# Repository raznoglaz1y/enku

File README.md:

<h1 align="center">ENKU</h1>

<p align="center">
  <strong>A pocketable e-reader you can actually own — repairable, local-first, distraction-free.</strong>
</p>

<p align="center">
  A focused, low-power 3.97″ reader with physical controls, local file management, no account or cloud requirement, and a documented, extensible hardware/software stack.
</p>

<p align="center">
  <strong>Project website:</strong> <a href="https://enkureader.com">enkureader.com</a>
</p>

<p align="center">
  <strong>UI languages:</strong> EN · PL · DE · FR · ES · IT · RU
</p>

---

## What is ENKU?

ENKU is a compact e-reader project currently validated around the **Waveshare ESP32-S3-ePaper-3.97** platform with an **800 × 480** e-paper display, while a dedicated portrait-first ENKU mainboard is being developed in parallel. The 3.97″ target is intentional: R0.1 remains a genuinely pocketable reader rather than growing into a small conventional e-reader.

The goal is not to reproduce a full tablet or build a feature-heavy general-purpose device. ENKU is intended to be a **small, calm and purpose-built reader**: fast enough for books, simple to operate, comfortable to use offline, and understandable from both the software and hardware side.

The project is being developed as a complete product system rather than only a firmware demo. It includes:

- firmware and device architecture;
- a complete non-touch UI for physical controls;
- library and reading workflows;
- typography and per-book settings;
- Wi-Fi and local browser-based file management;
- storage and import flows;
- sleep and power-management behavior;
- enclosure development and mechanical iterations;
- reproducible documentation for the hardware, firmware and enclosure;
- a custom ENKU mainboard and costed path toward small-batch community / kit builds.

> **Current status:** firmware architecture and reader runtime are actively implemented, while the custom ENKU R0.1 mainboard is in late routing / pre-production verification. Power routing and the USB-C connector/ESD/CC area have clean native KiCad checkpoints; USB data completion, dock/unrouted closure, final mechanical/electrical audit and the manufacturing package remain before fabrication. Features are only treated as complete when their repository checks or physical validation support that claim.

### Looking for hardware partners and component suppliers

ENKU is currently looking for **hardware partners, distributors and component suppliers** interested in supporting the development of the project.

The most useful forms of support at this stage are:

- Waveshare ESP32-S3-ePaper-3.97 development units;
- Li-Po batteries suitable for a compact e-reader enclosure;
- buttons, switches, fasteners and other enclosure hardware;
- prototype and replacement components for hardware testing;
- project discounts or sample units;
- technical information about supplied components;
- support for future hardware revisions and enclosure prototypes.

Partners can be credited in the project documentation and repository as hardware partners or component suppliers where appropriate.

The goal is to build ENKU around readily available, reproducible parts rather than one-off or inaccessible hardware.

For partnership or supply discussions, please open an issue or contact the project owner through GitHub.

## Custom mainboard and future kits

The reference Waveshare platform is useful for firmware bring-up, but ENKU is also being engineered as its own compact hardware platform.

The custom mainboard roadmap targets:
- ESP32-S3 + 3.97″ e-paper in a portrait-first PCB;
- physical page controls, hard power-off, BMI270 motion/orientation sensing and magnetic-cover support;
- USB-C as the primary charge/data connector;
- optional magnetic pogo/dock charging;
- a warm adjustable frontlight path promoted to production-candidate research after repeated community feedback;
- Pro-ready frontlight and wireless-charging population options;
- one core PCB that can support Base / Cover / Pro variants through DNP/population choices.

After validation, the project may offer small-batch **electronics kits, Base kits, magnetic-cover kits and Pro/frontlight kits**. These are planned possibilities rather than products currently for sale; final contents and pricing depend on tested hardware, sourcing, compliance and fulfillment.

The intent is to keep DIY builds fully documented even if assembled kits become available.

### Product decisions after the first community review

The first broad r/ereader review sharpened the product direction rather than changing the Pocket target. ENKU R0.1 stays at **3.97″**. The strongest recurring feedback was that open source alone is not enough differentiation, so the project is prioritizing the parts that must be better at the hardware/product level: **repairability, physical controls, battery life, screen-to-body ratio, direct USB storage access and a credible warm-frontlight path**.

The firmware roadmap now includes **USB Mass Storage / direct microSD access**, **Markdown reading**, and logical control remapping for left/right-handed use in portrait and landscape. CrossPoint compatibility will be investigated rather than treating community firmware as something ENKU should exclude.

A separate **compact 4.7–5.2″, preferably 4:3** hardware direction is being researched for later; it is not a replacement for the pocket 3.97″ device.

### R0.1 engineering checkpoint — October 2026

The dedicated ENKU mainboard has progressed beyond placement into detailed routing and verification. The current working baseline is intentionally kept **green in native KiCad CI** while remaining USB and dock routing is iterated.

Fabrication is gated on:

- complete USB D+/D− routing through connector-side ESD and series tuning resistors to ESP32-S3;
- dock detect/power closure and an explicit **zero-unrouted-connections** check;
- final power, EPD high-voltage, return-path, antenna keepout, connector-edge and repairability review;
- final footprint/orientation and mechanical-access audit;
- reproducible Gerber, NC drill, BOM and pick-and-place outputs plus a final PCBWay viewer review.

A green DRC alone is not considered a fabrication release: R0.1 must also pass the explicit connectivity and manufacturing gates above.

## Support ENKU

ENKU is developed publicly, while production-sensitive engineering may remain private until it is mature enough to release. You can help the project without spending money:

- **Star the repository** to make the project easier to discover.
- **Test and report issues** when firmware and hardware builds are available.
- **Contribute** code, documentation, translations, UI feedback, hardware notes or enclosure work — see [CONTRIBUTING.md](CONTRIBUTING.md).
- **Share ENKU** with people interested in open hardware, e-paper and compact readers.

GitHub Sponsors is the project's primary funding channel. Sponsorships help cover development hardware, prototype boards, batteries, enclosure iterations and other direct project costs.

**Sponsor ENKU:** https://github.com/sponsors/raznoglaz1y

Project contact and support page: **https://enkureader.com/contact**

## Follow the project

ENKU is entering its first public community-feedback stage. The immediate goal is to validate the reader, the custom R0.1 hardware and the mechanical design with e-reader, maker and repairability communities before any manufacturing commitment is made.

A **small production run / crowdfunding campaign is being considered after hardware validation**, but no campaign, launch date, price or production quantity is being promised yet. Development remains public and technical feedback is welcome now.

- Project site: https://enkureader.com
- GitHub: https://github.com/raznoglaz1y/enku
- Reddit launch draft: [docs/outreach/reddit-r-ereader.md](docs/outreach/reddit-r-ereader.md)
- Hackaday project draft: [docs/outreach/hackaday-project-draft.md](docs/outreach/hackaday-project-draft.md)

## Project goals

ENKU is being designed around a deliberately narrow set of product goals:

- provide a **comfortable, distraction-free reading experience** on a compact e-paper device;
- remain useful **fully offline**;
- use **physical controls** instead of depending on a touchscreen;
- keep book storage, reading progress and settings under the user's control;
- support a clean local workflow for importing and managing books;
- make the firmware, interfaces, hardware assumptions and repair path understandable, with source/design releases tied to product maturity;
- stay small enough to be a practical everyday reader rather than a general-purpose tablet.

## Non-goals

ENKU is **not** intended to become:

- an Android-like general-purpose device;
- a multimedia tablet;
- a cloud-dependent reading service;
- a storefront or DRM ecosystem;
- a notification-heavy connected gadget;
- a platform that hides core reading features behind an account.

The project favors a smaller, coherent feature set over adding functionality that does not improve reading.

## Why ENKU?

### Reading first

The interface is built around one job: **reading**. The reader screen stays visually quiet, controls appear only when needed, and common actions are reachable without navigating through deep menus.

### E-paper from the beginning

ENKU is designed specifically for e-paper constraints rather than adapting a conventional LCD interface afterward. Refresh behavior, focus states, progress updates, sleep screens and interaction density are all treated as part of the product architecture.

### Physical controls, no touchscreen dependency

The UI is designed for buttons and deterministic focus navigation. Focus, selected values and active states are separate concepts, which keeps the interface predictable and accessible without touch.

### Offline by default

Books remain usable without Wi-Fi. Connectivity is an optional management layer, not a requirement for reading.

### Open, understandable and user-owned

The project aims to document not only the final code, but also **why** design and implementation decisions were made. UI rules, navigation behavior and product decisions are documented publicly. Production-sensitive PCB, manufacturing and sourcing work may remain private during active development and be released selectively after the design stabilizes.

### Compact hardware target

A 3.97″ panel keeps the device small enough to carry easily while still providing a practical 800 × 480 reading canvas. Both portrait and landscape orientations are part of the design system.

## Design preview

The interface is being designed in English first and then localized. The boards below are current **EN design previews** from the active UI revision work; they are not yet firmware screenshots.

<table>
<tr>
<td width="50%"></td>
<td width="50%"></td>
</tr>
<tr>
<td align="center"><strong>Library</strong></td>
<td align="center"><strong>First start / Language</strong></td>
</tr>
<tr>
<td width="50%"></td>
<td width="50%"></td>
</tr>
<tr>
<td align="center"><strong>Book details</strong></td>
<td align="center"><strong>Library / List</strong></td>
</tr>
</table>

The production visual source of truth remains the Figma design system and approved review boards.

---

## Target hardware

The current reference platform is:

| Component | Target |
| --- | --- |
| Main board | Waveshare ESP32-S3-ePaper-3.97 |
| MCU | ESP32-S3 |
| Display | 3.97″ e-paper, 800 × 480 |
| Input | Up / Function / Down control + BOOT; PWR handled separately |
| Storage | microSD / local storage workflow |
| Connectivity | Wi-Fi, BLE available at platform level |
| Power | Li-Po battery; final pack and runtime profile to be validated on hardware |
| Enclosure | Custom 3D-printable case, developed after mechanical verification |

The current official Waveshare source maps the active-low navigation inputs to GPIO4 (Up), GPIO5 (Function), GPIO6 (Down) and GPIO0 (BOOT). ENKU keeps raw GPIO details inside the platform layer and maps them to stable logical actions. PWR is treated separately through the PMU. Physical behavior will still be verified on the received board.

### Parts status

| Part | Current status |
| --- | --- |
| Waveshare ESP32-S3-ePaper-3.97 | **Selected / ordered** |
| 3.97″ 800 × 480 e-paper panel | **Part of reference platform** |
| microSD storage | **Platform feature — hardware verification pending** |
| Li-Po battery | **TBD — ~2000 mAh target, final size/connector pending** |
| Physical controls | **Platform controls to be mapped and tested** |
| Power switch / enclosure hardware | **TBD** |
| Fasteners | **TBD after mechanical measurements** |
| 3D-printed enclosure | **Planned after hardware measurement** |

See the detailed [Hardware baseline](docs/hardware.md) and [BOM status](docs/bom.md).

## Planned reader experience

### Library

- grid and list views;
- persistent sort and filter state;
- All / New / Reading / Finished filters;
- Title / Author / Recently opened / Recently added sorting;
- global title/author search independent from the active browse filter;
- bounded/paged result queries for large libraries;
- book details and cover handling;
- reading-state indicators;
- progress persistence;
- empty/error states designed as first-class screens.

### Reading

**Reader v1 formats:** EPUB, FB2 and TXT. PDF is deferred to a later revision.

- distraction-free reading view;
- portrait and landscape;
- semantic position preservation after layout changes;
- table of contents;
- bookmarks;
- in-book search;
- finished-book state;
- restore to the previous reading position.

### Typography

Five built-in presets are planned:

**Spacious · Comfortable · Standard · Compact · Dense**

Each preset controls font size, line spacing and margins. Manual adjustment switches the book to **Custom**. Settings can be global or overridden per book.

The current reading typeface target is **Noto Sans**.

### Local file management

The first management workflow is intentionally local:

- upload one or many books from a browser on the same network;
- drag-and-drop transfer;
- view storage usage and free space;
- inspect and correct metadata;
- replace or remove covers;
- safely delete or replace book files;
- show import progress and errors;
- reset progress or per-book settings.

Reading itself does not depend on this web interface.

### Wi-Fi

Planned Wi-Fi behavior includes:

- saved networks;
- explicit trusted/preferred networks;
- deterministic reconnect behavior;
- password entry using the shared on-device keyboard;
- session-scoped local web management;
- no cloud account requirement.

### Sleep and power

ENKU separates **panel sleep**, **device suspend** and **full PMU power-off**.

- user-facing Sleep means a measured system-level low-power state, not only `EPD_Sleep()`;
- static sleep screens suitable for e-paper;
- optional book-cover sleep screen;
- Wi-Fi off during Sleep;
- no live clock or animation while sleeping;
- auto-sleep suspended during writes/imports;
- full Power Off uses the board PMU shutdown path;
- exact suspend mechanism, wake sources and battery thresholds are validated on real hardware.

---

## Current limitations

ENKU is still in the pre-firmware stage, so several important decisions remain intentionally open:

- there is no production reader firmware yet, but the first framework-neutral TXT parser, forward-pagination, Reader Engine and ReaderSession MVPs are now implemented and host-testable;
- a framework-neutral C++ firmware scaffold now exists under `firmware/`;
- the firmware architecture, Library/storage model, parser abstraction, pagination model and runtime state machine are specified, while hardware integration and reader implementation remain pending;
- Reader v1 is scoped to EPUB, FB2 and TXT; PDF support is deferred and not yet designed;
- the exact CBOR codec library, localization table generator, diagnostics backend and parser/rendering stack are not selected;
- the final system suspend mechanism and wake-source mapping have not yet been measured on the real board;
- partial/region refresh behavior and ghosting thresholds have not yet been measured on the real panel;
- battery model and real-world runtime are not finalized;
- physical button mapping and wake behavior still require hardware testing;
- the enclosure has not been dimensioned from the production board yet;
- current EN design boards are design previews, not screenshots from running firmware.

These are active development items, not hidden assumptions.

## Firmware direction

Firmware has not yet been published as a working reader. The planned implementation is split into clear subsystems so the project can evolve without coupling the UI directly to storage or parser internals.

### Core layers

1. **Hardware abstraction**
   - display driver and refresh policy;
   - buttons and input events;
   - storage;
   - Wi-Fi;
   - battery/power state.

2. **Application state / Library**
   - stable `book_id`-based Library records;
   - bounded Browse/Search query model;
   - library index;
   - current book;
   - reading position;
   - bookmarks;
   - settings;
   - network state.

3. **Reader engine**
   - shared normalized parser/document interfaces;
   - first TXT parser MVP implemented in C++;
   - first forward text-pagination MVP implemented in C++;
   - first concrete DocumentReaderEngine implemented over the paginator;
   - ReaderSession with deterministic visited-page Previous and previous/current/next working-set cache;
   - Reader runtime integration updates AppState/progress and emits PageTurn refresh requests;
   - Open → Reading, Back → Library checkpoint and Finished transitions are now modeled in runtime;
   - concrete TXT book-loader/document-provider owns BookDocument → ReaderEngine → ReaderSession lifetime;
   - EPUB and FB2 parser adapters still pending;
   - normalized metadata/document model;
   - on-demand pagination using a font/text measurement abstraction;
   - typography presets;
   - semantic position mapping;
   - search and table of contents.

4. **Runtime and startup**
   - staged boot with boot-loop detection;
   - Normal / First Start / Recovery boot modes;
   - deterministic book open / page navigation;
   - Reader Menu and Search context;
   - debounced progress persistence;
   - sleep/wake restoration;
   - recoverable error handling.

5. **UI system**
   - reusable status bar, headers, rows, buttons and dialogs;
   - focus navigation;
   - portrait/landscape layout;
   - localization through stable semantic string keys;
   - English fallback with generated compact locale tables;
   - render plans describing only visible changes.

6. **Refresh Manager**
   - Region / Full / Deferred / None update classes;
   - bounded serialized refresh queue;
   - dirty-region coalescing and stale-plan removal;
   - measured ghosting/full-refresh escalation;
   - panel-refresh diagnostics.

7. **Persistence layer**
   - versioned CBOR records;
   - separate Library / settings / per-book state;
   - A/B generation recovery;
   - debounced progress checkpoints;
   - schema migration and integrity validation.

8. **Diagnostics and recovery**
   - stable structured error codes;
   - localized user-facing error mapping;
   - bounded in-memory logs;
   - compact critical/reboot diagnostics;
   - boot-loop detection and Recovery/Safe Mode.

9. **Local management service**
   - upload/import;
   - metadata operations;
   - storage status;
   - safe replace/delete transactions.

A framework-neutral C++ interface scaffold now exists under [firmware/](firmware/). The exact framework, build system, display library and parser stack will be chosen after display bring-up, memory profiling and real-device tests.

---

## Enclosure development

The enclosure is a separate project track, not an afterthought.

The plan is to develop the case in stages:

1. **Mechanical verification**
   - measure the production board;
   - verify display stack height, connectors, controls and battery space;
   - establish safe internal clearances.

2. **Functional prototype**
   - simple printable shell;
   - reliable access to controls and charging;
   - battery retention;
   - serviceable assembly.

3. **Ergonomic iteration**
   - comfortable grip;
   - practical button placement;
   - reduced thickness where mechanically safe;
   - portrait and landscape handling.

4. **Production-ready open model**
   - printable case files;
   - screw/assembly specification;
   - tolerances and print notes;
   - alternative battery/case variants where useful.

No final mechanical dimensions will be published as authoritative until the actual hardware is measured.

---

## Project roadmap

**At a glance:**  
**Design system → Hardware bring-up → Reader MVP → Connectivity → Enclosure → Open release**

### Phase 1 — Product and UI foundation

- [x] Define ENKU product direction
- [x] Select Waveshare ESP32-S3-ePaper-3.97 as reference platform
- [x] Define non-touch interaction model
- [x] Build reusable UI foundations and component rules
- [x] Audit the initial screen set
- [x] Define EN as the canonical UI language
- [ ] Finish canonical EN review boards
- [ ] Complete storage/import and Wi-Fi screen revisions

### Phase 2 — Hardware bring-up

- [ ] Verify board revision and physical controls
- [ ] Bring up the e-paper panel
- [ ] Characterize full/partial refresh behavior and ghosting
- [ ] Verify microSD and persistent storage
- [ ] Measure Active / DisplayIdle / Suspended / PoweredOff current
- [ ] Validate wake/power-off behavior
- [ ] Confirm typography rendering and memory use

### Phase 3 — Reader MVP

- [x] Select Reader v1 formats: EPUB, FB2 and TXT; PDF deferred
- [ ] Implement staged boot coordinator and first-usable-screen checkpoint
- [ ] Implement Refresh Manager queue and render-plan pipeline
- [x] Connect PageNext/PagePrevious runtime events to ReaderSession/AppState
- [x] Implement Reader open/back/finished runtime transitions
- [ ] Connect the firmware scaffold to verified platform drivers
- [x] Add ReaderSession page history/cache and deterministic Previous
- [ ] Expand pagination beyond TXT paragraphs and add real font metrics
- [ ] Implement EPUB/FB2 parsers and complete text layout
- [ ] Implement LibraryService/index and grid/list navigation
- [ ] Implement CBOR persistence and reading-position checkpoints
- [ ] Implement typography presets and Custom mode
- [ ] Add bookmarks and table of contents
- [ ] Add in-book search
- [ ] Add sleep/restore flow

### Phase 4 — Import and connectivity

- [ ] microSD import
- [ ] validation and duplicate handling
- [ ] local Wi-Fi upload
- [ ] browser-based library management
- [ ] metadata and cover editing
- [ ] transactional replace/delete behavior
- [ ] interruption and recovery handling

### Phase 5 — Enclosure

- [ ] Measure final hardware
- [ ] Build first functional case prototype
- [ ] Test battery placement and assembly
- [ ] Refine ergonomics
- [ ] Publish printable enclosure files and assembly notes

### Phase 6 — Release quality

- [ ] Finalize canonical EN string catalog
- [ ] Add RU/PL/DE/FR/ES/IT UI translations
- [ ] Validate missing-key fallback and long translated strings
- [ ] Run portrait/landscape layout validation
- [ ] Test malformed books, missing storage and interrupted transfers
- [ ] Validate reboot and power-loss recovery
- [ ] Validate boot-loop detection, Recovery Mode and diagnostic export
- [ ] Publish reproducible build instructions
- [x] Define software/documentation/hardware licensing model
- [ ] Tag the first public reader release

A more detailed implementation roadmap lives in [ROADMAP.md](ROADMAP.md).

---

## UI and design system

The UI source of truth is being developed in Figma and documented in this repository.

Key rules:

- non-touch interaction;
- focus is not the same as selection;
- both **800 × 480 landscape** and **480 × 800 portrait** are supported;
- 24 px standard screen inset;
- 48 px baseline button/input height;
- safe default focus for destructive dialogs;
- English is the canonical source language;
- e-paper refresh limitations are treated as product constraints.

Useful documents:

- [Project status](docs/status.md)
- [Architecture](docs/architecture.md)
- [Firmware project structure](docs/firmware-structure.md)
- [Input & physical controls](docs/input-model.md)
- [Power, sleep & wake model](docs/power-model.md)
- [Reader runtime & state machine](docs/runtime-state-machine.md)
- [Pagination & rendering model](docs/pagination-model.md)
- [Pagination MVP](docs/pagination-mvp.md)
- [Reader Engine MVP](docs/reader-engine-mvp.md)
- [Reader Session MVP](docs/reader-session-mvp.md)
- [Reader Runtime Integration MVP](docs/reader-runtime-mvp.md)
- [Book Loader / Document Provider MVP](docs/book-loader-mvp.md)
- [Metadata & parser model](docs/parser-model.md)
- [Licensing model](LICENSES.md)
- [Library & storage model](docs/storage-model.md)
- [Library data model & service interface](docs/library-model.md)
- [Persistence backend](docs/persistence-model.md)
- [Localization architecture](docs/localization-model.md)
- [Errors, logging & diagnostics](docs/diagnostics-model.md)
- [Boot & startup architecture](docs/boot-model.md)
- [Refresh Manager & e-paper update policy](docs/refresh-model.md)
- [Hardware baseline](docs/hardware.md)
- [BOM status](docs/bom.md)
- [UI specification](docs/ui-spec.md)
- [UI audit](docs/ui-audit.md)
- [UI revision plan](docs/ui-revision-plan.md)
- [Screen inventory](docs/screens.md)
- [Navigation model](docs/navigation.md)

## Repository structure

```text
assets/
  branding/         ENKU identity assets

design/
  screens/          historical and current UI boards
  renders/          project diagrams and visual references

firmware/
  README.md                firmware scaffold status and entry point
  include/enku/            framework-neutral core/input/reader/service interfaces

docs/
  architecture.md          system architecture
  firmware-structure.md    source layout and module boundaries
  input-model.md            physical controls and logical input mapping
  power-model.md            panel sleep, system suspend and PMU power-off
  runtime-state-machine.md  reader runtime and recovery behavior
  pagination-model.md       text layout and pagination rules
  pagination-mvp.md         first TXT → BookDocument → page implementation
  reader-engine-mvp.md      first BookDocument → Reader PageResult bridge
  reader-session-mvp.md     deterministic Next/Previous session navigation
  reader-runtime-mvp.md     page events → AppState → refresh integration
  book-loader-mvp.md        Library/source → parser → ReaderSession lifecycle
  parser-model.md           metadata normalization and parser abstraction
  storage-model.md          Library identity, state and transactional storage
  library-model.md          book records, browse/search queries and LibraryService
  persistence-model.md      CBOR records, schema versioning and crash recovery
  localization-model.md     string keys, fallback, plurals and locale packaging
  diagnostics-model.md      structured errors, bounded logs and Recovery Mode
  boot-model.md             staged startup, restore and boot-loop handling
  refresh-model.md          render plans, refresh queue and ghosting policy
  hardware.md              verified/planned hardware baseline
  bom.md                   parts/BOM status and sourcing priorities
  status.md                current project status
  UI and interaction specifications

locales/
  README.md          localization source-catalog rules

README.md           project overview
ROADMAP.md          implementation roadmap
NOTICE.md           third-party asset and release notes
```

The `firmware/` directory now contains the framework-neutral interface scaffold. Hardware-specific implementations and build files will be added after verified board bring-up. Hardware and enclosure source directories will be added when those workstreams contain verified material.

## Localization

**English is the canonical/source UI language.**

Planned first localization wave:

- English
- Russian
- Polish
- German
- French
- Spanish
- Italian

The interface language is independent from book content and keyboard input mode.

ENKU uses English as the canonical/fallback string set, stable semantic keys, named placeholders and a lightweight centralized plural system. Human-readable locale sources are intended to be converted into compact runtime lookup tables rather than parsed as JSON on the device.

## Licensing and source-release policy

ENKU uses a scoped multi-license model for material that is published:

- **Firmware/software:** Apache License 2.0
- **Project documentation:** Creative Commons Attribution 4.0 International (CC BY 4.0)
- **Future project-owned hardware/mechanical source:** CERN Open Hardware Licence Version 2 — Permissive (CERN-OHL-P-2.0)

The ENKU name/logo, historical design boards and third-party assets are not automatically covered by those blanket grants. Their scope and release requirements are documented in [LICENSES.md](LICENSES.md) and [NOTICE.md](NOTICE.md).

GitHub language detection is configured through `.gitattributes` so implementation source is represented by its actual code language instead of documentation/design assets dominating repository statistics.

---

<p align="center">
  <strong>ENKU is being built as a real reading device: small, focused, open and understandable.</strong>
</p>

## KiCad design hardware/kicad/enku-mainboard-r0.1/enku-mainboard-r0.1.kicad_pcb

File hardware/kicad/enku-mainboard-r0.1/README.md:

# ENKU Mainboard R0.1 — KiCad worktree

> **Frontlight provenance gate (2026-10-05):** any October 2 TPS923610/10 µH/15 Ω/selector baseline in this document is historical, not fabrication-authoritative. Keep the Pro frontlight population DNP until the clean manufacturer-source re-derivation in `docs/HARDWARE_PROVENANCE.md` is complete.

This directory contains the CAD worktree for the custom ENKU mainboard.

Current state:
- portrait 54 × 94 mm four-layer PCB;
- mounting-hole baseline;
- ESP32 antenna, Qi, buttons, microSD, USB-C, Dock and hard-power zones;
- first mechanically sensitive component placement has started;
- J_EPD uses the R0.1 dual-contact 24-pin connector baseline;
- J_FL uses the R0.1 dual-contact 6-pin connector baseline;
- EPD 47 µH inductor and boost MOSFET are now represented in the placement;
- Pro frontlight driver zone and remap field are represented;
- no routing yet.

Important:
- schematic capture remains authoritative for nets and final footprint synchronization;
- several footprints in the PCB are marked as R0.1 placement placeholders and must be replaced/verified against manufacturer land patterns before fabrication;
- no KiCad ERC/DRC has been run in the current environment;
- this is **not fabrication-ready**.

Companion:
- [Placement baseline A](PLACEMENT_R01.md)
- `../../../docs/schematic-netlist-r01.md`
- `../../../docs/r01-blocker-closure.md`

Next:
1. capture the complete schematic;
2. assign/verify exact manufacturer footprints;
3. update the PCB from schematic;
4. reconcile the first placement with actual courtyard/keepout data;
5. route;
6. run ERC/DRC in KiCad;
7. generate PCBWay files only from the checked KiCad project.

## Schematic hierarchy

R0.1 now has a real KiCad hierarchical capture baseline:

- `enku-mainboard-r0.1.kicad_sch` — root sheet
- `power.kicad_sch` — USB/Dock arbitration, charger, hard-off 3.3 V path
- `mcu_io.kicad_sch` — ESP32-S3-WROOM-1-N16R8, shared SPI, I2C, buttons, Hall/IMU/ADC assignments
- `epd_hv.kicad_sch` — 24-pin EPD FPC and SSD1677 external-HV interface boundary
- `frontlight.kicad_sch` — TPS923610 path, 6-pin raw FPC and 0R/DNP remap boundary
- `connectors.kicad_sch` — USB-C, dock, debug and DNP Qi interface

These files are schematic-capture baselines, not a fabrication release. The next gate is to expand the remaining block-level circuits into exact discrete symbols, review every footprint, and run KiCad ERC before routing is treated as electrically authoritative.

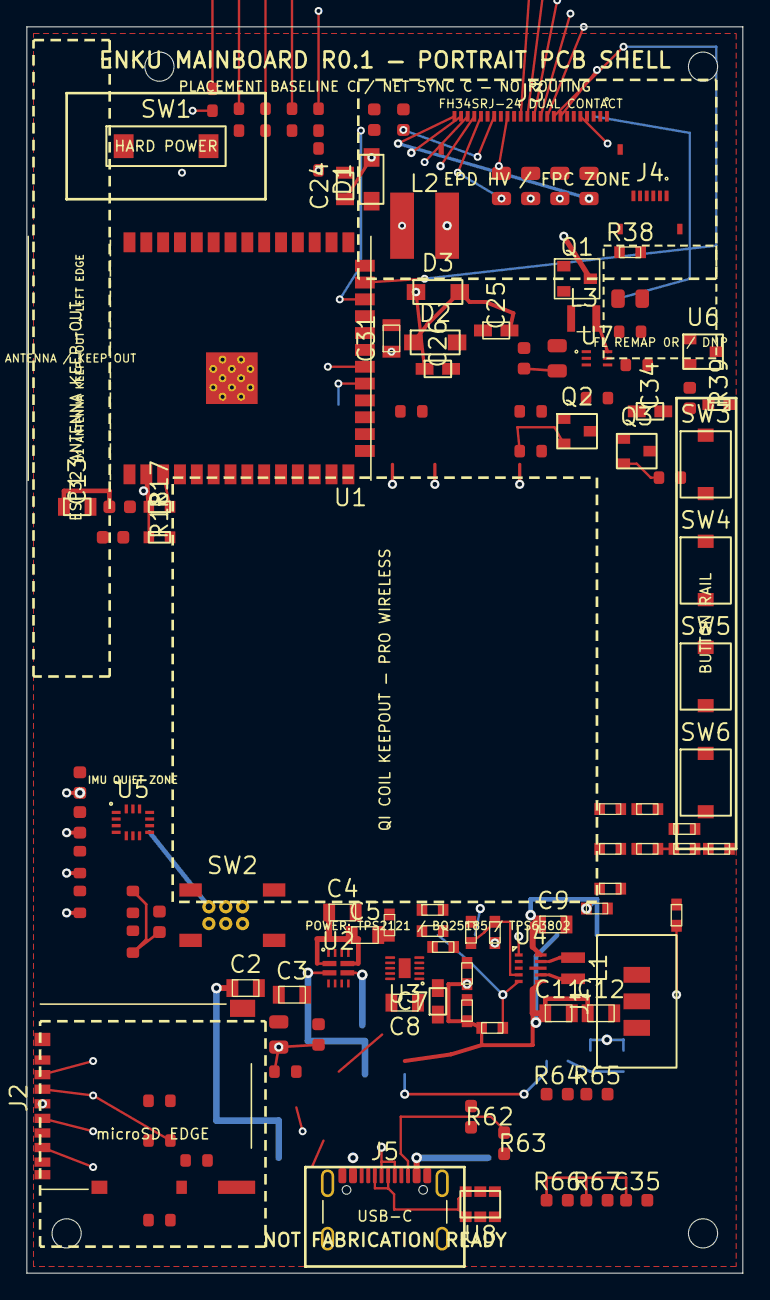
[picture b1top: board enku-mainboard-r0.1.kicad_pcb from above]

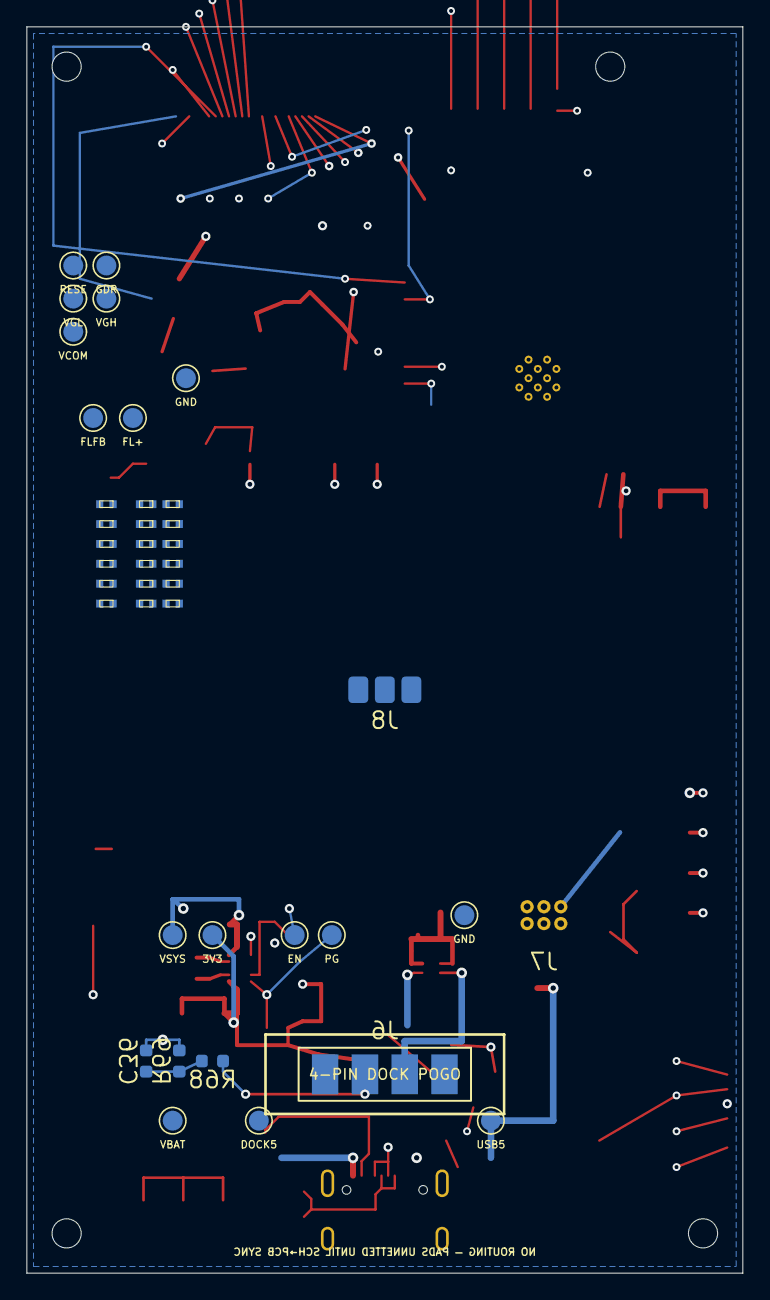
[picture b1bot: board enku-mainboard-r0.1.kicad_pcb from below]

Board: 4 copper layers, 54.0 x 94.0 mm, 156 parts (40 on the bottom side), 92 nets.

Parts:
C1, C10, C14, C17, C18, C19, C20, C21, C33: 100nF; C_0603_1608Metric
C2, C3, C4, C9, C13, C16: 10uF 10V; C_0805_2012Metric
C5, C24, C25, C26, C27, C28, C29, C31: 4.7uF 25V; C_0805_2012Metric
C6: 100nF 25V; C_0603_1608Metric
C7: 10uF 25V; C_0805_2012Metric
C8, C32: 4.7uF 10V; C_0805_2012Metric
C11, C12: 22uF 10V; C_0805_2012Metric
C15: 1uF; C_0603_1608Metric
C22, C23: 1uF 25V; C_0603_1608Metric
C30: 1uF 25V X7R; C_0805_2012Metric
C34: 4.7uF 50V; C_0805_2012Metric
C35: 4.7nF; C_0603_1608Metric
C36: 10nF; C_0603_1608Metric
D1, D2, D3: MBR0530; D_SOD-123
H1, H2, H3, H4: MountingHole_2.2mm_M2
J1: 1S LiPo + NTC; JST_PH_3_PLACEMENT
J2: Hirose DM3AT-SF-PEJM5; MICROSD_DM3AT_ENKU
J3: FH34SRJ-24S-0.5SH(50); FH34SRJ-24S-0.5SH
J4: FH34SRJ-6S-0.5SH(50); FH34SRJ-6S-0.5SH
J5: GCT USB4105-GF-A-120; USB_C_Receptacle_GCT_USB4105-xx-A_16P_TopMnt_Horizontal
J6: 4-pin pogo dock; DOCK_POGO_4
J7: Tag-Connect TC2030-IDC-NL; Tag-Connect_TC2030-IDC-NL_2x03_P1.27mm_Vertical
J8: Pro Wireless Qi raw interface — DNP; QI_RAW_3
L1: 0.47uH DFE201612E-R47M=P2; Murata_DFE201612E
L2: 10uH TYS5040100M-10; TYS5040_5x5
L3: 10uH VLS252012HBX-100M-1; TDK_VLS252012
Q1: IRLML6346TRPBF; SOT-23
Q2, Q3: BSS138LT1G; SOT-23
R1: 100k 1%; R_0603_1608Metric
R2, R3, R4, R5: 0R STRAP; R_0603_1608Metric
R6, R7, R19, R28, R29, R41: 0R; R_0603_1608Metric
R8: 18k 1%; R_0603_1608Metric
R9: 1k 1%; R_0603_1608Metric
R10, R13, R16, R35, R36, R40, R42, R43, R69: 100k; R_0603_1608Metric
R11, R17, R18, R68: 10k; R_0603_1608Metric
R12: 10k DNP; R_0603_1608Metric
R14: 511k 1%; R_0603_1608Metric
R15: 91k 1%; R_0603_1608Metric
R20, R21, R22, R64, R65: 0R (22R tune); R_0603_1608Metric
R23: 47k; R_0603_1608Metric
R24, R25: 4.7k; R_0603_1608Metric
R26: 2M 1%; R_0603_1608Metric
R27: 680k 1%; R_0603_1608Metric
R30, R31, R32, R33, R34: 22R; R_0603_1608Metric
R37: 2.2R 1% 0805; R_0805_2012Metric
R38: 1M 1%; R_0603_1608Metric
R39: 15R 1%; R_0603_1608Metric
R44, R45, R46, R47, R48, R49, R50, R51, R52, R53, R54, R55, R56, R57, R58, R59, R60, R61: 0R DNP; R_0402_1005Metric
R62, R63: 5.1k 1%; R_0603_1608Metric
R66: 1M; R_0603_1608Metric
R67: 0R DNP; R_0603_1608Metric
SW1: HARD POWER; HARD_POWER_SWITCH_PLACEMENT
SW2: BOOT / RECOVERY; SW_SPST_TL3342
SW3: BTN_PREV; READING_BUTTON_PLACEMENT
SW4: BTN_NEXT; READING_BUTTON_PLACEMENT
SW5: BTN_SELECT; READING_BUTTON_PLACEMENT
SW6: BTN_BACK; READING_BUTTON_PLACEMENT
TP1, TP14: GND; TestPoint_Pad_D1.5mm
TP2: VBUS_USB; TestPoint_Pad_D1.5mm
TP3: VBUS_DOCK; TestPoint_Pad_D1.5mm
TP4: VBAT; TestPoint_Pad_D1.5mm
TP5: VSYS; TestPoint_Pad_D1.5mm
TP6: 3V3_SYS; TestPoint_Pad_D1.5mm
TP7: SYS_EN; TestPoint_Pad_D1.5mm
TP8: REG_PG; TestPoint_Pad_D1.5mm
TP9: EPD_GDR; TestPoint_Pad_D1.5mm
TP10: EPD_RESE; TestPoint_Pad_D1.5mm
TP11: EPD_VGH; TestPoint_Pad_D1.5mm
TP12: EPD_VGL; TestPoint_Pad_D1.5mm
TP13: EPD_VCOM; TestPoint_Pad_D1.5mm
TP15: FL_LED_PLUS; TestPoint_Pad_D1.5mm
TP16: FL_FB; TestPoint_Pad_D1.5mm
U1: ESP32-S3-WROOM-1-N16R8; ESP32-S3-WROOM-1
U2: TPS2121; TPS2121_RUX0012A
U3: BQ25185DLHR; BQ25185_DLH0010A
U4: TPS63802DLAR; TPS63802_DLA0010A
U5: BMI270; BMI270_Bosch_LGA14
U6: DRV5032FBDBZR; SOT-23
U7: TPS923610DRLR; TPS923610_DRL0006A
U8: USBLC6-2SC6; SOT-23-6

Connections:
3V3_SYS: C11.1, C12.1, C13.1, C14.1, C16.1, C17.1, C18.1, C19.1, C20.1, J2.4, J3.15, J7.1, R11.1, R12.1, R14.1, R16.1, R17.1, R18.1, R23.1, R24.1, R25.1, R28.1, R35.1, R36.1, TP6.1, U1.2, U4.6, U5.5, U5.8, U5.12, U6.1
BAT_ADC: C21.1, R26.2, R27.1, U1.39
BAT_TS: J1.3, U3.6
BOOT: J7.5, R18.2, SW2.1, U1.27
BTN_BACK: SW6.1, U1.7
BTN_NEXT: SW4.1, U1.5
BTN_PREV: SW3.1, U1.4
BTN_SELECT: SW5.1, U1.6
CHG_CE_N: R10.1, U3.4
CHG_ILIM_VSET: R8.1, U3.7
CHG_ISET: R9.1, U3.8
CHG_STAT1: R11.2, U1.8, U3.9
CHG_STAT2: R12.2, U3.3
DOCK_DETECT: C36.1, R68.2, R69.1, U1.38
DOCK_DETECT_RAW: J6.3, R68.1
EPD_BS1: J3.8, R29.1
EPD_BUSY: J3.9, U1.25
EPD_CP_NEG: C25.2, D2.2, D3.1
EPD_CS: R32.1, U1.22
EPD_CS_PANEL: J3.12, R32.2, R35.2
EPD_DC: R31.1, U1.23
EPD_DC_PANEL: J3.11, R31.2
EPD_GDR: J3.2, Q1.1, R38.1, TP9.1
EPD_MOSI_PANEL: J3.14, R34.2
EPD_RESE: J3.3, Q1.2, R37.1, TP10.1
EPD_RST: R30.1, U1.24
EPD_RST_PANEL: J3.10, R30.2, R36.2
EPD_SCLK_PANEL: J3.13, R33.2
EPD_SW: C25.1, D1.2, L2.2, Q1.3
EPD_VCI: C22.1, C31.1, J3.16, L2.1, R28.2
EPD_VCOM: C30.1, J3.24, TP13.1
EPD_VDD: C23.1, J3.18
EPD_VGH: C24.1, D1.1, J3.21, TP11.1
EPD_VGL: C26.1, D3.2, J3.23, TP12.1
EPD_VSH1: C27.1, J3.20
EPD_VSH2: C28.1, J3.5
EPD_VSL: C29.1, J3.22
ESP_EN: C15.1, J7.6, R17.2, U1.3
FL_ADIM: R40.1, R41.2, U7.2
FL_COOL_PWM: Q3.1, R43.1, U1.33
FL_COOL_RETURN: Q3.3, R46.2, R49.2, R52.2, R55.2, R58.2, R61.2
FL_ENABLE: R41.1, U1.34
FL_FB: Q2.2, Q3.2, R39.1, TP16.1, U7.3
FL_LED_PLUS: C34.1, R44.2, R47.2, R50.2, R53.2, R56.2, R59.2, TP15.1, U7.5
FL_RAW1: J4.1, R44.1, R45.1, R46.1
FL_RAW2: J4.2, R47.1, R48.1, R49.1
FL_RAW3: J4.3, R50.1, R51.1, R52.1
FL_RAW4: J4.4, R53.1, R54.1, R55.1
FL_RAW5: J4.5, R56.1, R57.1, R58.1
FL_RAW6: J4.6, R59.1, R60.1, R61.1
FL_SW: L3.2, U7.6
FL_WARM_PWM: Q2.1, R42.1, U1.32
FL_WARM_RETURN: Q2.3, R45.2, R48.2, R51.2, R54.2, R57.2, R60.2
GND: C1.2, C2.2, C3.2, C4.2, C5.2, C6.2, C7.2, C8.2, C9.2, C10.2, C11.2, C12.2, C13.2, C14.2, C15.2, C16.2, C17.2, C18.2, C19.2, C20.2, C21.2, C22.2, C23.2, C24.2, C26.2, C27.2, C28.2, C29.2, C30.2, C31.2, C32.2, C33.2, C34.2, C35.2, C36.2, D2.1, J1.2, J2.6, J3.17, J3.S1, J3.S2, J4.S1, J4.S2, J5.A1, J5.A12, J5.B1, J5.B12, J6.1, J6.4, J7.2, J8.3, R1.2, R3.2, R5.2, R6.2, R7.2, R8.2, R9.2, R10.2, R13.2, R15.2, R27.2, R29.2, R37.2, R38.2, R39.2, R40.2, R42.2, R43.2, R62.2, R63.2, R66.2, R67.2, R69.2, SW2.2, SW3.2, SW4.2, SW5.2, SW6.2, TP1.1, TP14.1, U1.1, U1.40, U1.41, U2.12, U3.5, U3.11, U4.2, U4.3, U4.8, U5.1, U5.6, U5.7, U6.3, U7.4, U8.2
HALL_INT: U1.10, U6.2
I2C_SCL: R25.2, U1.17, U5.13
I2C_SDA: R24.2, U1.12, U5.14
IMU_INT1: U1.11, U5.4
MUX_CP2: R4.2, R5.1, U2.3
MUX_ILIM: R1.1, U2.10
MUX_OV1: R6.1, U2.5
MUX_OV2: R7.1, U2.4
MUX_PR1: R2.2, R3.1, U2.6
MUX_SS: C1.1, U2.11
QI_STATUS: J8.2, U1.9
REG_FB: R14.2, R15.1, U4.4
REG_L1: L1.1, U4.9
REG_L2: L1.2, U4.7
REG_PG: R16.2, TP8.1, U4.5
SD_CS: R19.1, U1.18
SD_CS_CARD: J2.2, R19.2, R23.2
SD_MISO_CARD: J2.7, R22.1
SD_MOSI_CARD: J2.3, R20.2
SD_SCLK_CARD: J2.5, R21.2
SPI_MISO: R22.2, U1.21
SPI_MOSI: R20.1, R34.1, U1.19
SPI_SCLK: R21.1, R33.1, U1.20
SYS_EN: R13.1, SW1.2, TP7.1, U4.1
UART_RX: J7.4, U1.36
UART_TX: J7.3, U1.37
USB_CC1: J5.A5, R62.1
USB_CC2: J5.B5, R63.1
USB_DM: R65.2, U1.13
USB_DM_CONN: J5.A7, J5.B7, R65.1, U8.3, U8.4
USB_DP: R64.2, U1.14
USB_DP_CONN: J5.A6, J5.B6, R64.1, U8.1, U8.6
USB_SHIELD: C35.1, J5.S, R66.1, R67.1
VBAT: C8.1, J1.1, R26.1, TP4.1, U3.2
VBUS_DOCK: C3.1, J6.2, R4.1, TP3.1, U2.2
VBUS_EXT: C4.1, C5.1, C6.1, U2.1, U2.8, U3.10
VBUS_USB: C2.1, J5.A4, J5.A9, J5.B4, J5.B9, R2.1, TP2.1, U2.7, U8.5
VSYS: C7.1, C9.1, C10.1, C32.1, C33.1, L3.1, SW1.1, TP5.1, U3.1, U4.10, U7.1
